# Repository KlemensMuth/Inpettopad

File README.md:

# InpettoPad

The InpettoPad is a 6 Key Macropad featuring 2 rotary encoder,  
an OLED display and a built in clock feature! It´s using <br>
QMK Firmware and ONLY runs on MacOS.

# Features:

- Bottom and Top 3D Printed Case
- 128x32 OLED Display
- 2x EC11 Rotary encoder
- 6x MX-Style Switches

# Cad Model:

Everything fits together using 4 3D printed "Screws". The PCB itself is lying on a podest inside the case. <br>
It´s printed in 3 Parts: <br>
The 4 "Screws" <br>
The upper Case <br>
The lower Case <br>

## Quick picture of the Case:

# PCB and Schematic

## Heres my PCB and Shematic, which were both made in KiCad.

 <br>
*I used "MX_PUSH" from KiCAd for the keyswitch footprints.*

# Firware
Used abriviations: <br>
P/H = Press and Hold<br>
S. Press = Press<br>
d. press = Double Press<br>
X/X = Row(In assembeled Key board) / Position in Row ( 0, 1, 2) ** 0 being all the way down/ to the left<br>
r.t.l/r. = rotate to left/right<br><br>

## Functions:<br>
   Display Lock (Key,0/0) [S. press -> Lock Display, d. press -> shutdown menu]<br>
   ShortCut to Claude/AI of your choice (Key, 0/1) [S. press -> AI]<br>
   ScreenShot(Key, 0/2) [S. press -> Screenshot, P/H -> Recording]<br>
   AudioPlayer(Key, 1/1) [S. Press -> Play/pause, d. press -> previous Song, P/H -> Skip Song]<br>
   Light Controle(Key, 1/2) [S. press -> Light toggle]ts and link it to either the application or a web link of your favourite AI.<br>
   Focus Toggle(Key, 1/0) [S. press -> Focus toggle] <br>
   Volume Controle(Rotary Encoder, Right) [r.t.r. -> Volume Up, r.t.l. -> Volume Down, S. press -> Mute Audio]<br>
   FullScreen Toggle(Rotary Encoder, Left) [r.t.l/r. -> Switch to either Full or not-Full screen]<br>
   Clock(Rotary Encoder, Left) [s. press -> Enter Clock setting mode THEN AFTER S.PRESS r.t.l/r -> Set Time]<br><br>

## SetUp: <br>
Due to non existing Keyboard Commands on MacOS some Functions have to be SetUp in Apple Shortcuts!!<br>

### 1. Shortcut to CLaude:<br>
To set Up enter the KeyCombination (Left Command, Left Shift and C) in a new Shortcut in Apple Shortcuand link it to Apple Home Smart Home remote conrole.<br>
### 2. Light Controle:<br>
To set Up enter the KeyCombination (Left Command, Left Shift and L) in a new Shortcut in Apple Shortcuts <br>
### 3. Focus Toggle:<br>
To set Up enter the KeyCombination (Left Command, Left Shift and F) in a new Shortcut in Apple Shortcuts and set it to enable/disable your Focus of choice.

# BOM
### Here should be everything you need to make this hackpad <br><br>
6x Cherry MX Switches<br>
6x DSA Keycaps<br>
8x 1N4148 DO-35 Diodes.<br>
1x 0.91" 128x32 OLED Display<br>
2x EC11 Rotary Encoder<br>
1x XIAO RP2040<br>
1x Case (3 printed parts)<br>

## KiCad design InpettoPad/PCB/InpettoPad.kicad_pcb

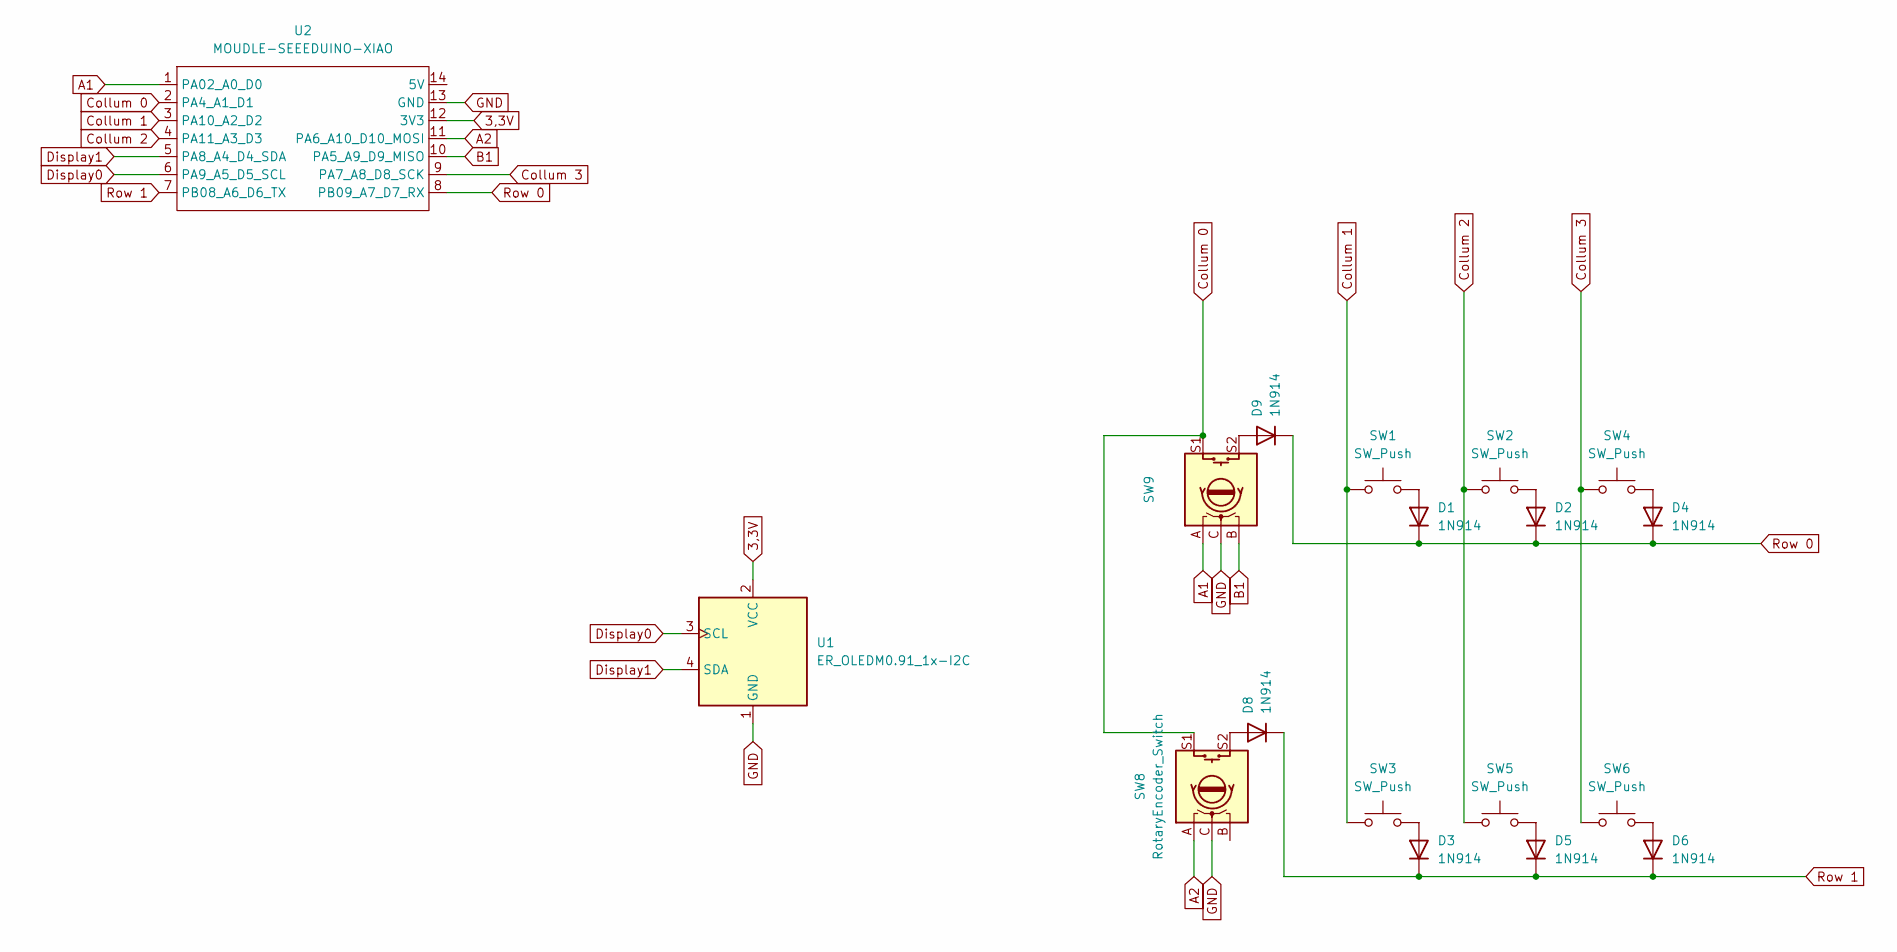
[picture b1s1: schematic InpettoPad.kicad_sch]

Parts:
D1, D2, D3, D4, D5, D6, D8, D9: 1N914; D_DO-35_SOD27_P7.62mm_Horizontal
SW1, SW2, SW3, SW4, SW5, SW6: SW_Push; SW_Cherry_MX_1.00u_PCB
SW8, SW9: RotaryEncoder_Switch; RotaryEncoder_Alps_EC11E-Switch_Vertical_H20mm
U1: ER_OLEDM0.91_1x-I2C
U2: MOUDLE-SEEEDUINO-XIAO; MODULE_102010428

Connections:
3,3V: U1.2 (VCC), U2.12 (3V3)
A1: SW9.A, U2.1 (PA02_A0_D0)
A2: SW8.A, U2.11 (PA6_A10_D10_MOSI)
B1: SW9.B, U2.10 (PA5_A9_D9_MISO)
Collum 0: SW8.S1, SW9.S1, U2.2 (PA4_A1_D1)
Collum 1: SW1.1, SW3.1, U2.3 (PA10_A2_D2)
Collum 2: SW2.1, SW5.1, U2.4 (PA11_A3_D3)
Collum 3: SW4.1, SW6.1, U2.9 (PA7_A8_D8_SCK)
Display0: U1.3 (SCL), U2.6 (PA9_A5_D5_SCL)
Display1: U1.4 (SDA), U2.5 (PA8_A4_D4_SDA)
GND: SW8.C, SW9.C, U1.1 (GND), U2.13 (GND)
unnamed: D1.2 (A), SW1.2
unnamed: D2.2 (A), SW2.2
unnamed: D3.2 (A), SW3.2
unnamed: D4.2 (A), SW4.2
unnamed: D5.2 (A), SW5.2
unnamed: D6.2 (A), SW6.2
unnamed: D8.2 (A), SW8.S2
unnamed: D9.2 (A), SW9.S2
Row 0: D1.1 (K), D2.1 (K), D4.1 (K), D9.1 (K), U2.8 (PB09_A7_D7_RX)
Row 1: D3.1 (K), D5.1 (K), D6.1 (K), D8.1 (K), U2.7 (PB08_A6_D6_TX)

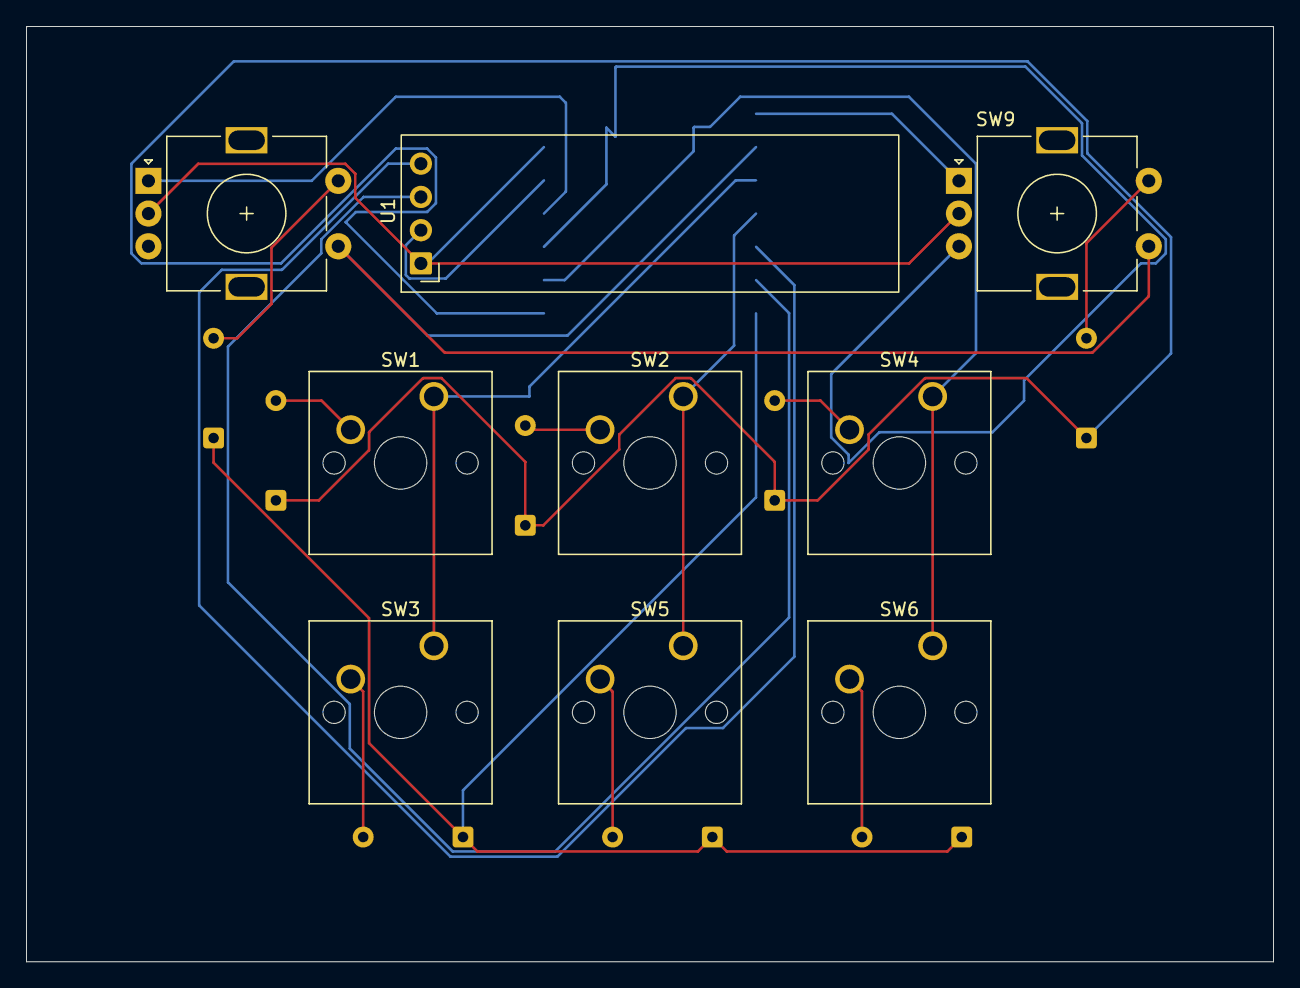
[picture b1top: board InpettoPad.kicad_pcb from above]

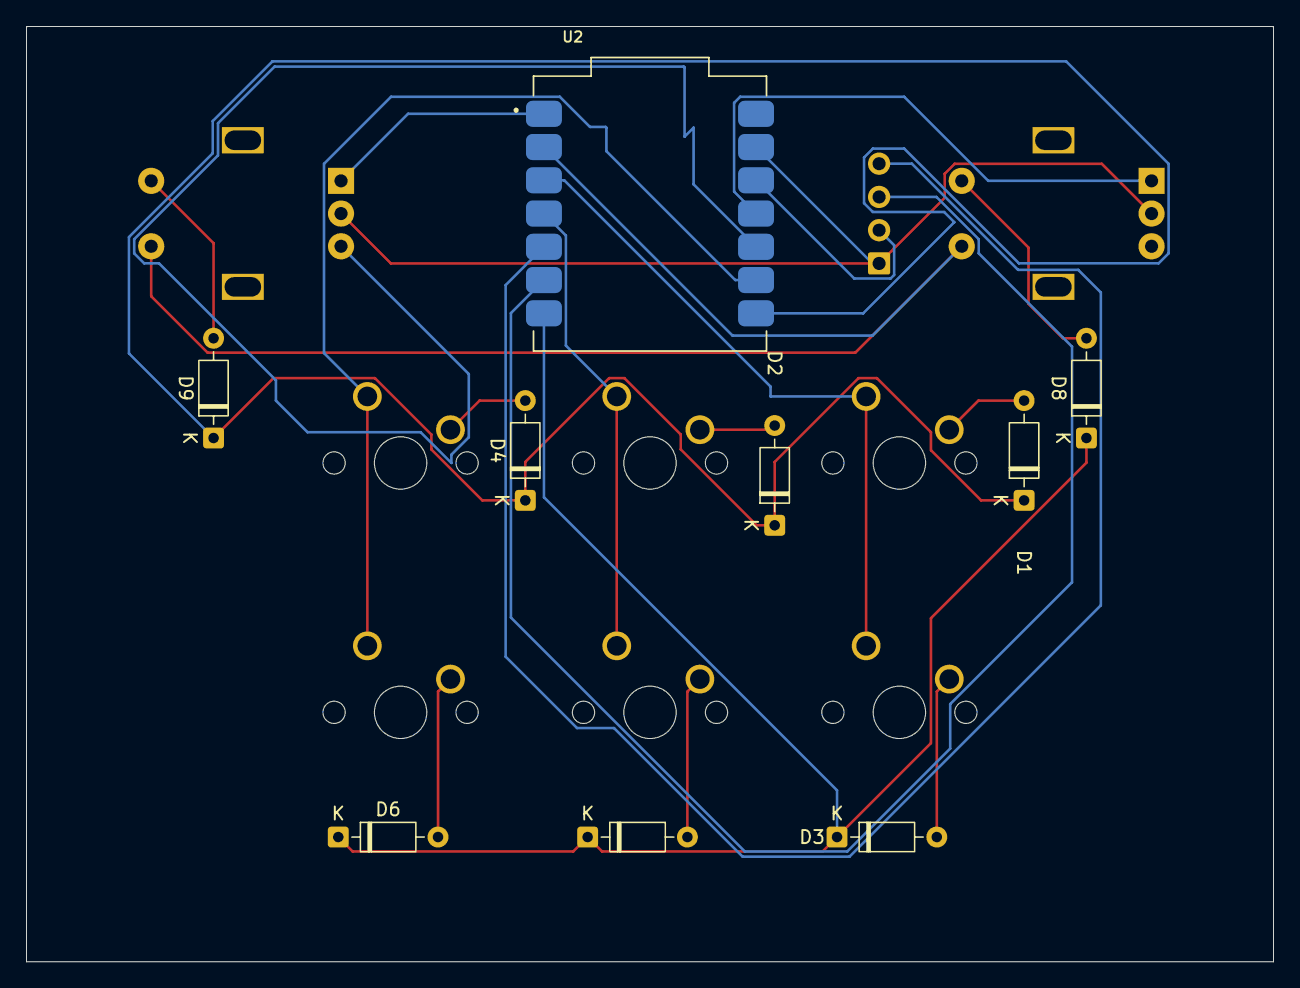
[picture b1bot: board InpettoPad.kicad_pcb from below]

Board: 2 copper layers, 95.2 x 71.4 mm, 18 parts (9 on the bottom side), 21 nets.
